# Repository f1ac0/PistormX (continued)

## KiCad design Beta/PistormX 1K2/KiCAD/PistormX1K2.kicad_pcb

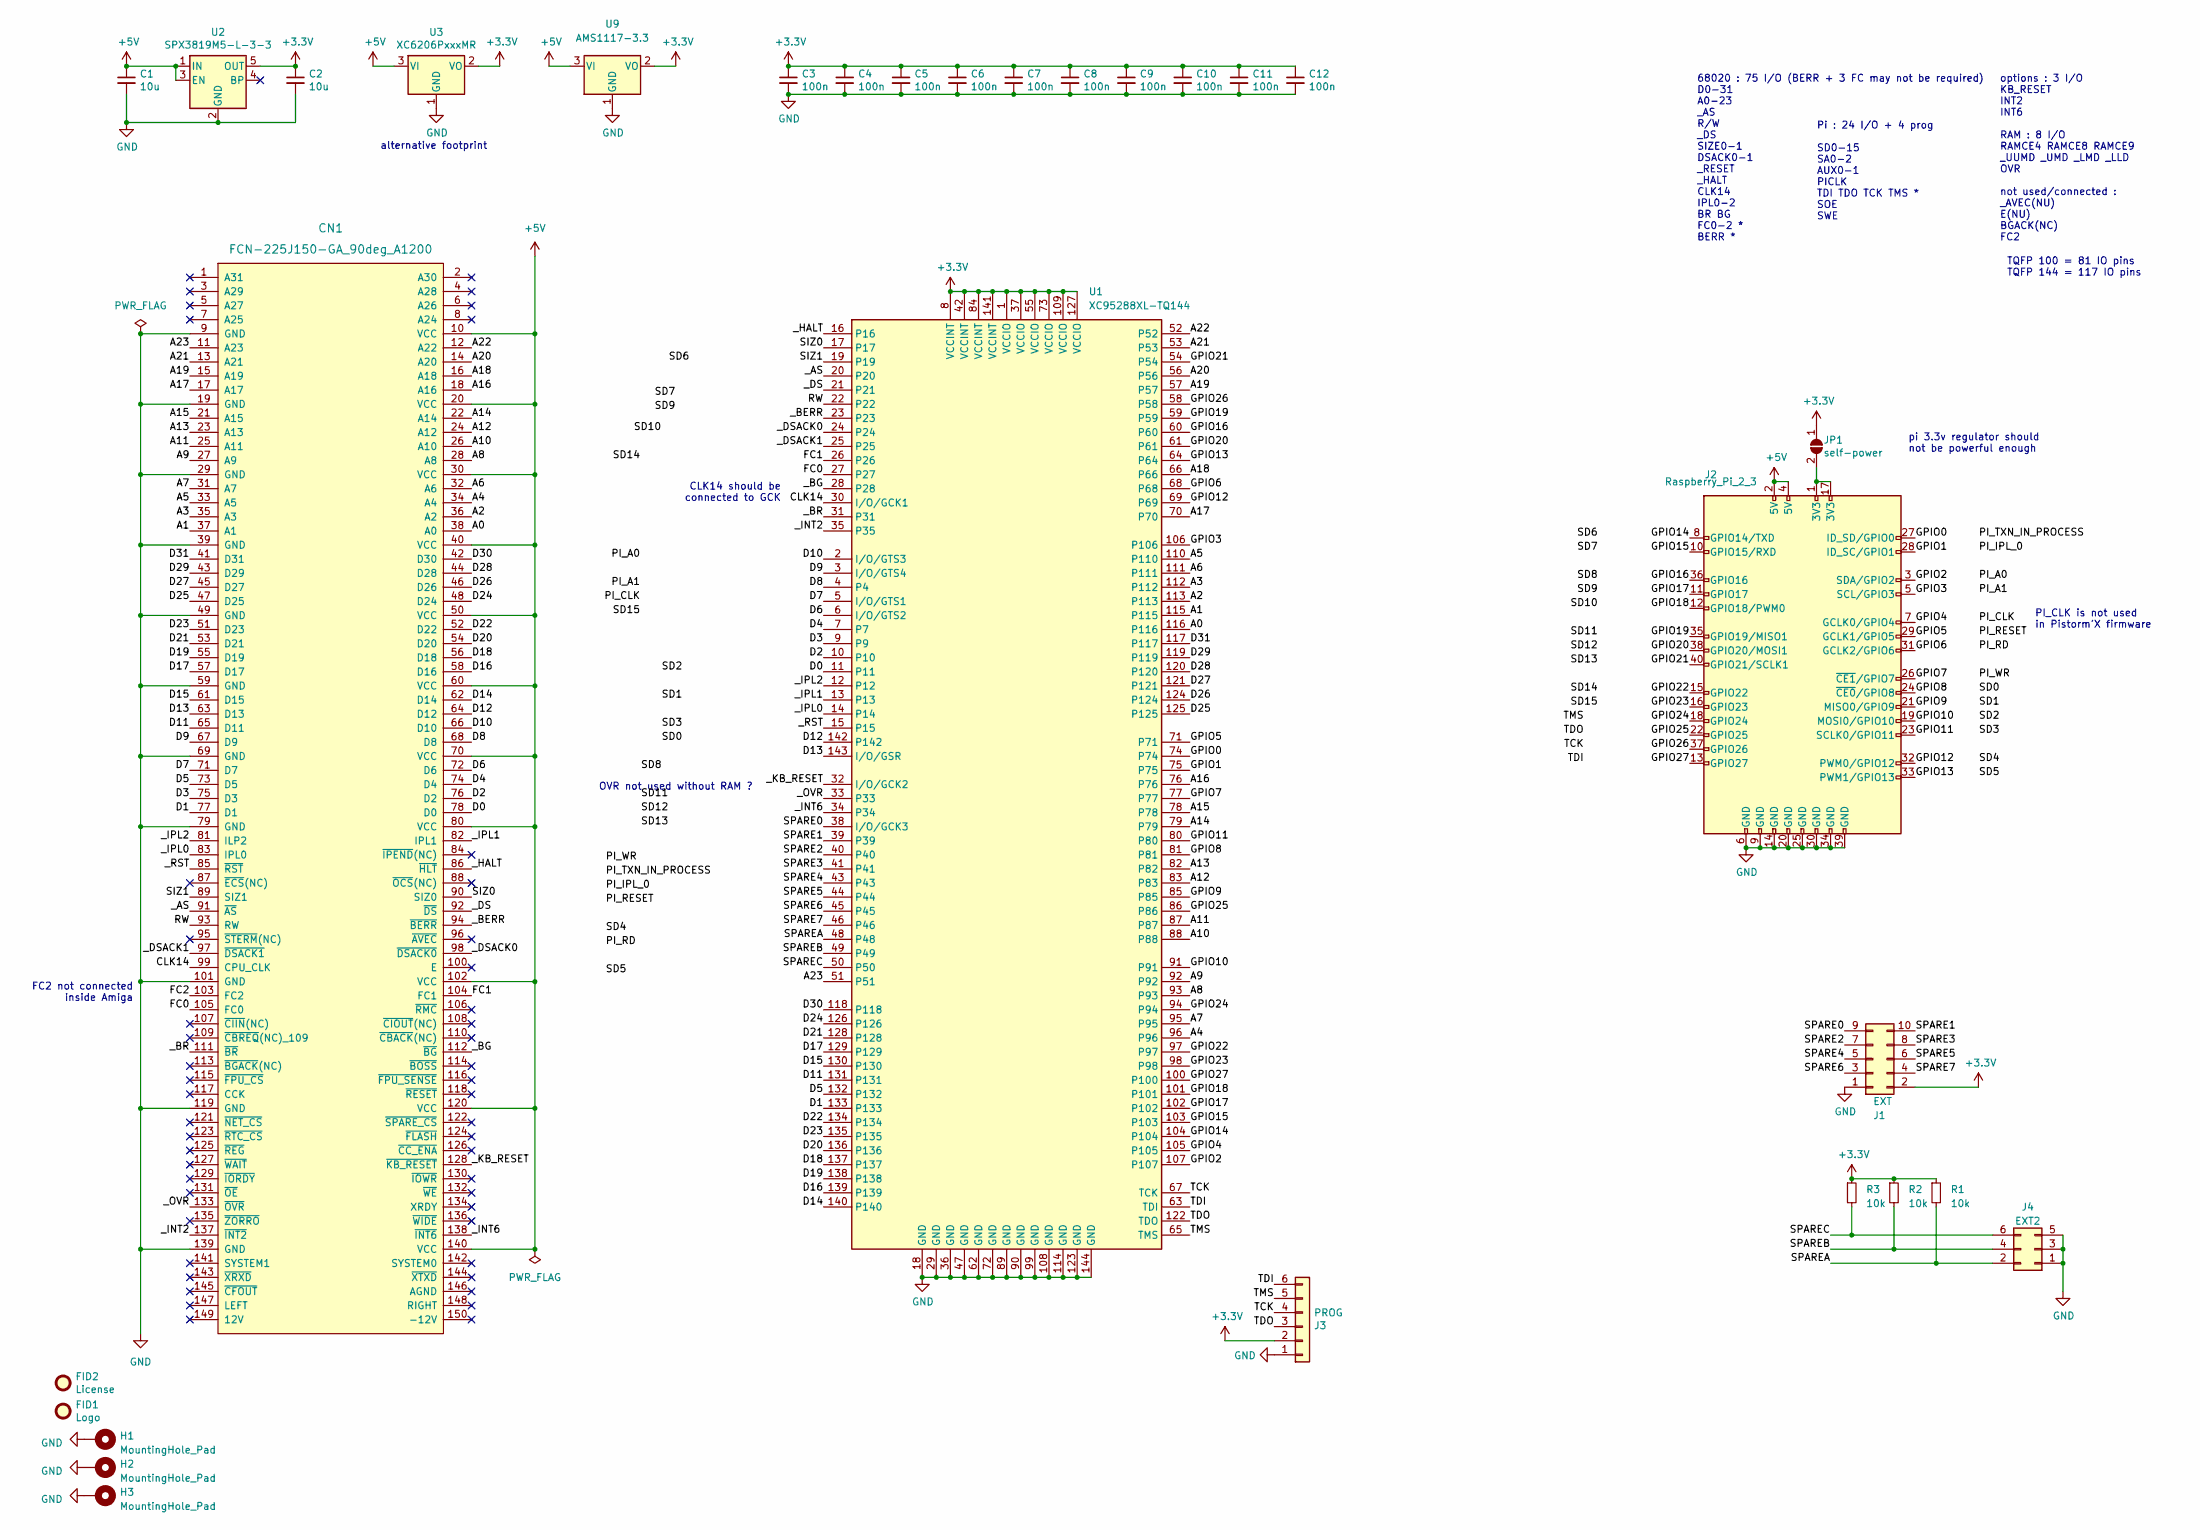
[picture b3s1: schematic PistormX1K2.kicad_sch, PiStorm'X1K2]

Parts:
C1, C2: 10u; C_0805_2012Metric
C3, C4, C5, C6, C7, C8, C9, C10, C11, C12: 100n; C_0603_1608Metric
CN1: FCN-225J150-GA_90deg_A1200
FID1: Logo; PIC_PistormX_43x10mm
FID2: License; CC_BY_NC_SA_square_silkscreen
H1, H2, H3: MountingHole_Pad; MountingHole_2.7mm_M2.5_DIN965_Pad
J1: EXT; PinHeader_2x05_P2.54mm_Vertical
J2: Raspberry_Pi_2_3; PinSocket_2x20_P2.54mm_Vertical_SMD_BottomEntry
J3: PROG; PinHeader_1x06_P2.54mm_Vertical
J4: EXT2; PinHeader_2x03_P2.54mm_Vertical
JP1: self-power; SolderJumper-2_P1.3mm_Open_RoundedPad1.0x1.5mm
R1, R2, R3: 10k; R_0805_2012Metric
U1: XC95288XL-TQ144; TQFP-144_20x20mm_P0.5mm
U2: SPX3819M5-L-3-3; SOT-23-5
U3: XC6206PxxxMR; SOT-23
U9: AMS1117-3.3; SOT-223-3_TabPin2

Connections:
+3.3V: C2.1, C3.1, C4.1, C5.1, C6.1, C7.1, C8.1, C9.1, C10.1, C11.1, C12.1, J1.2, J3.2, JP1.1 (A), R1.1, R2.1, R3.1, U1.1 (VCCIO), U1.8 (VCCINT), U1.37 (VCCIO), U1.42 (VCCINT), U1.55 (VCCIO), U1.73 (VCCIO), U1.84 (VCCINT), U1.109 (VCCIO), U1.127 (VCCIO), U1.141 (VCCINT), U2.5 (OUT), U3.2 (VO), U9.2 (VO)
+5V: C1.1, CN1.10 (VCC), CN1.20 (VCC), CN1.30 (VCC), CN1.40 (VCC), CN1.50 (VCC), CN1.60 (VCC), CN1.70 (VCC), CN1.80 (VCC), CN1.102 (VCC), CN1.120 (VCC), CN1.140 (VCC), J2.2 (5V), J2.4 (5V), U2.1 (IN), U2.3 (EN), U3.3 (VI), U9.3 (VI)
/A0: CN1.38 (A0), U1.116
/A1: CN1.37 (A1), U1.115
/A2: CN1.36 (A2), U1.113
/A3: CN1.35 (A3), U1.112
/A4: CN1.34 (A4), U1.96
/A5: CN1.33 (A5), U1.110
/A6: CN1.32 (A6), U1.111
/A7: CN1.31 (A7), U1.95
/A8: CN1.28 (A8), U1.93
/A9: CN1.27 (A9), U1.92
/A10: CN1.26 (A10), U1.88
/A11: CN1.25 (A11), U1.87
/A12: CN1.24 (A12), U1.83
/A13: CN1.23 (A13), U1.82
/A14: CN1.22 (A14), U1.79
/A15: CN1.21 (A15), U1.78
/A16: CN1.18 (A16), U1.76
/A17: CN1.17 (A17), U1.70
/A18: CN1.16 (A18), U1.66
/A19: CN1.15 (A19), U1.57
/A20: CN1.14 (A20), U1.56
/A21: CN1.13 (A21), U1.53
/A22: CN1.12 (A22), U1.52
/A23: CN1.11 (A23), U1.51
/CLK14: CN1.99 (CPU_CLK), U1.30 (I/O/GCK1)
/D0: CN1.78 (D0), U1.11
/D1: CN1.77 (D1), U1.133
/D2: CN1.76 (D2), U1.10
/D3: CN1.75 (D3), U1.9
/D4: CN1.74 (D4), U1.7
/D5: CN1.73 (D5), U1.132
/D6: CN1.72 (D6), U1.6 (I/O/GTS2)
/D7: CN1.71 (D7), U1.5 (I/O/GTS1)
/D8: CN1.68 (D8), U1.4
/D9: CN1.67 (D9), U1.3 (I/O/GTS4)
/D10: CN1.66 (D10), U1.2 (I/O/GTS3)
/D11: CN1.65 (D11), U1.131
/D12: CN1.64 (D12), U1.142
/D13: CN1.63 (D13), U1.143 (I/O/GSR)
/D14: CN1.62 (D14), U1.140
/D15: CN1.61 (D15), U1.130
/D16: CN1.58 (D16), U1.139
/D17: CN1.57 (D17), U1.129
/D18: CN1.56 (D18), U1.137
/D19: CN1.55 (D19), U1.138
/D20: CN1.54 (D20), U1.136
/D21: CN1.53 (D21), U1.128
/D22: CN1.52 (D22), U1.134
/D23: CN1.51 (D23), U1.135
/D24: CN1.48 (D24), U1.126
/D25: CN1.47 (D25), U1.125
/D26: CN1.46 (D26), U1.124
/D27: CN1.45 (D27), U1.121
/D28: CN1.44 (D28), U1.120
/D29: CN1.43 (D29), U1.119
/D30: CN1.42 (D30), U1.118
/D31: CN1.41 (D31), U1.117
/FC0: CN1.105 (FC0), U1.27
/FC1: CN1.104 (FC1), U1.26
/FC2: CN1.103 (FC2)
/GPIO0: J2.27 (ID_SD/GPIO0), U1.74
/GPIO1: J2.28 (ID_SC/GPIO1), U1.75
/GPIO2: J2.3 (SDA/GPIO2), U1.107
/GPIO3: J2.5 (SCL/GPIO3), U1.106
/GPIO4: J2.7 (GCLK0/GPIO4), U1.105
/GPIO5: J2.29 (GCLK1/GPIO5), U1.71
/GPIO6: J2.31 (GCLK2/GPIO6), U1.68
/GPIO7: J2.26 (~CE1/GPIO7), U1.77
/GPIO8: J2.24 (~CE0/GPIO8), U1.81
/GPIO9: J2.21 (MISO0/GPIO9), U1.85
/GPIO10: J2.19 (MOSI0/GPIO10), U1.91
/GPIO11: J2.23 (SCLK0/GPIO11), U1.80
/GPIO12: J2.32 (PWM0/GPIO12), U1.69
/GPIO13: J2.33 (PWM1/GPIO13), U1.64
/GPIO14: J2.8 (GPIO14/TXD), U1.104
/GPIO15: J2.10 (GPIO15/RXD), U1.103
/GPIO16: J2.36 (GPIO16), U1.60
/GPIO17: J2.11 (GPIO17), U1.102
/GPIO18: J2.12 (GPIO18/PWM0), U1.101
/GPIO19: J2.35 (GPIO19/MISO1), U1.59
/GPIO20: J2.38 (GPIO20/MOSI1), U1.61
/GPIO21: J2.40 (GPIO21/SCLK1), U1.54
/GPIO22: J2.15 (GPIO22), U1.97
/GPIO23: J2.16 (GPIO23), U1.98
/GPIO24: J2.18 (GPIO24), U1.94
/GPIO25: J2.22 (GPIO25), U1.86
/GPIO26: J2.37 (GPIO26), U1.58
/GPIO27: J2.13 (GPIO27), U1.100
/RW: CN1.93 (RW), U1.22
/SIZ0: CN1.90 (SIZ0), U1.17
/SIZ1: CN1.89 (SIZ1), U1.19
/SPARE0: J1.9, U1.38 (I/O/GCK3)
/SPARE1: J1.10, U1.39
/SPARE2: J1.7, U1.40
/SPARE3: J1.8, U1.41
/SPARE4: J1.5, U1.43
/SPARE5: J1.6, U1.44
/SPARE6: J1.3, U1.45
/SPARE7: J1.4, U1.46
/SPAREA: J4.2, R1.2, U1.48
/SPAREB: J4.4, R2.2, U1.49
/SPAREC: J4.6, R3.2, U1.50
/TCK: J3.4, U1.67 (TCK)
/TDI: J3.6, U1.63 (TDI)
/TDO: J3.3, U1.122 (TDO)
/TMS: J3.5, U1.65 (TMS)
/_AS: CN1.91 (~AS), U1.20
/_BERR: CN1.94 (~BERR), U1.23
/_BG: CN1.112 (~BG), U1.28
/_BR: CN1.111 (~BR), U1.31
/_DS: CN1.92 (~DS), U1.21
/_DSACK0: CN1.98 (~DSACK0), U1.24
/_DSACK1: CN1.97 (~DSACK1), U1.25
/_HALT: CN1.86 (~HLT), U1.16
/_INT2: CN1.137 (~INT2), U1.35
/_INT6: CN1.138 (~INT6), U1.34
/_IPL0: CN1.83 (IPL0), U1.14
/_IPL1: CN1.82 (IPL1), U1.13
/_IPL2: CN1.81 (ILP2), U1.12
/_KB_RESET: CN1.128 (~KB_RESET), U1.32 (I/O/GCK2)
/_OVR: CN1.133 (~OVR), U1.33
/_RST: CN1.85 (~RST), U1.15
GND: C1.2, C2.2, C3.2, C4.2, C5.2, C6.2, C7.2, C8.2, C9.2, C10.2, C11.2, C12.2, CN1.9 (GND), CN1.19 (GND), CN1.29 (GND), CN1.39 (GND), CN1.49 (GND), CN1.59 (GND), CN1.69 (GND), CN1.79 (GND), CN1.101 (GND), CN1.119 (GND), CN1.139 (GND), H1.1, H2.1, H3.1, J1.1, J2.6 (GND), J2.9 (GND), J2.14 (GND), J2.20 (GND), J2.25 (GND), J2.30 (GND), J2.34 (GND), J2.39 (GND), J3.1, J4.1, J4.3, J4.5, U1.18 (GND), U1.29 (GND), U1.36 (GND), U1.47 (GND), U1.62 (GND), U1.72 (GND), U1.89 (GND), U1.90 (GND), U1.99 (GND), U1.108 (GND), U1.114 (GND), U1.123 (GND), U1.144 (GND), U2.2 (GND), U3.1 (GND), U9.1 (GND)
unnamed: J2.1 (3V3), J2.17 (3V3), JP1.2 (B)

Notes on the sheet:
CLK14 should be connected to GCK
Pi : 24 I/O + 4 prog SD0-15 SA0-2 AUX0-1 PICLK TDI TDO TCK TMS * SOE SWE
OVR not used without RAM ?
FC2 not connected inside Amiga
alternative footprint
pi 3.3v regulator should not be powerful enough
TQFP 100 = 81 IO pins TQFP 144 = 117 IO pins
68020 : 75 I/O (BERR + 3 FC may not be required) D0-31 A0-23 _AS R/W _DS SIZE0-1 DSACK0-1 _RESET _HALT CLK14 IPL0-2 BR BG FC0-2 * BERR *
options : 3 I/O KB_RESET INT2 INT6 RAM : 8 I/O RAMCE4 RAMCE8 RAMCE9 _UUMD _UMD _LMD _LLD OVR not used/connected : _AVEC(NU) E(NU) BGACK(NC) FC2
PI_CLK is not used in Pistorm'X firmware

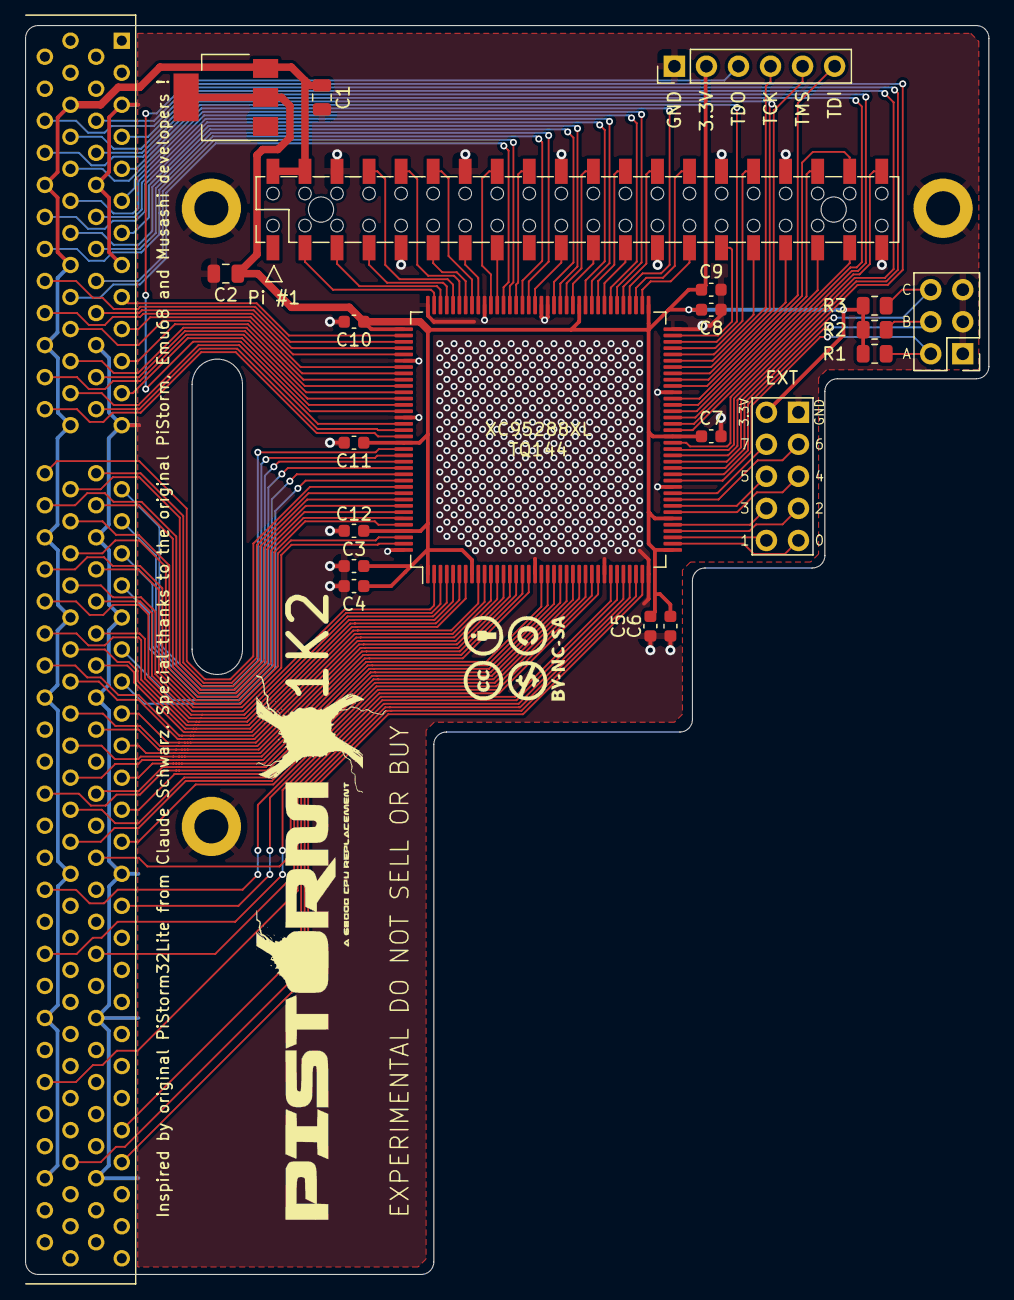
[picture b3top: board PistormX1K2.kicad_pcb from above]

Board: 2 copper layers, 76.4 x 99.0 mm, 27 parts (1 on the bottom side), 125 nets.

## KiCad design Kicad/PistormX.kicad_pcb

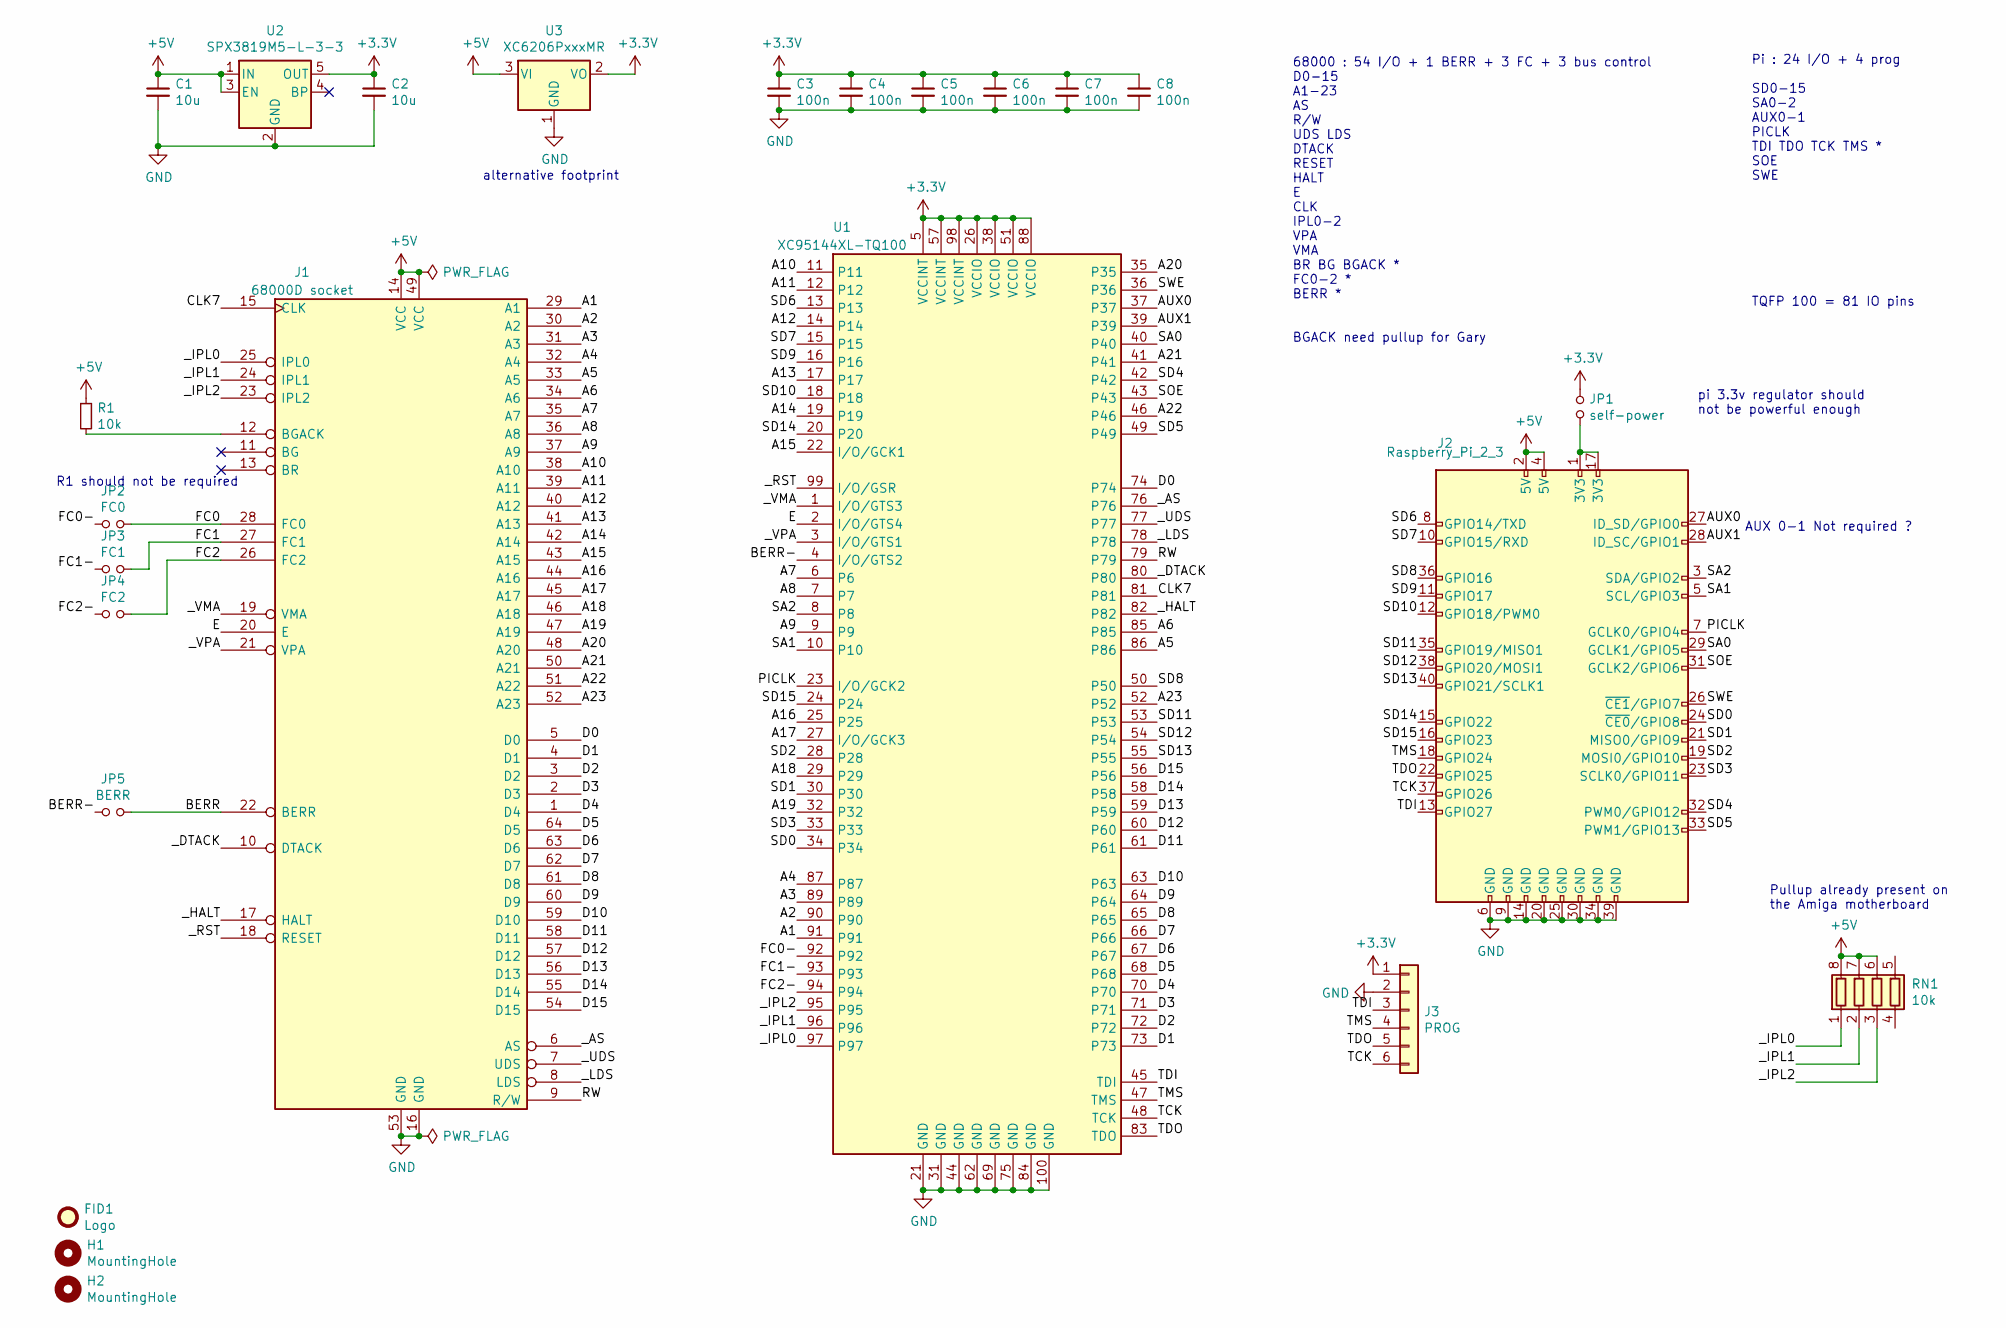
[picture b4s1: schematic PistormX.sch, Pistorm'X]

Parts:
C1, C2: 10u; C_0805_2012Metric
C3, C4, C5, C6, C7, C8: 100n; C_0805_2012Metric
FID1: Logo; PistormX
H1, H2: MountingHole; MountingHole_2.5mm
J1: 68000D socket; DIP-64_W22.86mm_BigPads1.4
J2: Raspberry_Pi_2_3; PinSocket_2x20_P2.54mm_Vertical
J3: PROG; PinHeader_1x06_P2.54mm_Vertical
JP1: self-power; SolderJumper-2_P1.3mm_Open_RoundedPad1.0x1.5mm
JP2: FC0; SolderJumper-2_P1.3mm_Open_RoundedPad1.0x1.5mm
JP3: FC1; SolderJumper-2_P1.3mm_Open_RoundedPad1.0x1.5mm
JP4: FC2; SolderJumper-2_P1.3mm_Open_RoundedPad1.0x1.5mm
JP5: BERR; SolderJumper-2_P1.3mm_Open_RoundedPad1.0x1.5mm
R1: 10k; R_0805_2012Metric
RN1: 10k; R_Array_Convex_4x0603
U1: XC95144XL-TQ100; TQFP-100_14x14mm_P0.5mm
U2: SPX3819M5-L-3-3; SOT-23-5
U3: XC6206PxxxMR; SOT-23

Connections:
+3V3: C2.1, C3.1, C4.1, C5.1, C6.1, C7.1, C8.1, J3.1, JP1.1, U1.5 (VCCINT), U1.26 (VCCIO), U1.38 (VCCIO), U1.51 (VCCIO), U1.57 (VCCINT), U1.88 (VCCIO), U1.98 (VCCINT), U2.5 (OUT), U3.2 (VO)
+5V: C1.1, J1.14 (VCC), J1.49 (VCC), J2.2 (5V), J2.4 (5V), R1.1, RN1.6 (R3.2), RN1.7 (R2.2), RN1.8 (R1.2), U2.1 (IN), U2.3 (EN), U3.3 (VI)
/A1: J1.29 (A1), U1.91
/A2: J1.30 (A2), U1.90
/A3: J1.31 (A3), U1.89
/A4: J1.32 (A4), U1.87
/A5: J1.33 (A5), U1.86
/A6: J1.34 (A6), U1.85
/A7: J1.35 (A7), U1.6
/A8: J1.36 (A8), U1.7
/A9: J1.37 (A9), U1.9
/A10: J1.38 (A10), U1.11
/A11: J1.39 (A11), U1.12
/A12: J1.40 (A12), U1.14
/A13: J1.41 (A13), U1.17
/A14: J1.42 (A14), U1.19
/A15: J1.43 (A15), U1.22 (I/O/GCK1)
/A16: J1.44 (A16), U1.25
/A17: J1.45 (A17), U1.27 (I/O/GCK3)
/A18: J1.46 (A18), U1.29
/A19: J1.47 (A19), U1.32
/A20: J1.48 (A20), U1.35
/A21: J1.50 (A21), U1.41
/A22: J1.51 (A22), U1.46
/A23: J1.52 (A23), U1.52
/BERR: J1.22 (BERR), JP5.2 (B)
/BERR-: JP5.1 (A), U1.4 (I/O/GTS2)
/CLK7: J1.15 (CLK), U1.81
/D0: J1.5 (D0), U1.74
/D1: J1.4 (D1), U1.73
/D2: J1.3 (D2), U1.72
/D3: J1.2 (D3), U1.71
/D4: J1.1 (D4), U1.70
/D5: J1.64 (D5), U1.68
/D6: J1.63 (D6), U1.67
/D7: J1.62 (D7), U1.66
/D8: J1.61 (D8), U1.65
/D9: J1.60 (D9), U1.64
/D10: J1.59 (D10), U1.63
/D11: J1.58 (D11), U1.61
/D12: J1.57 (D12), U1.60
/D13: J1.56 (D13), U1.59
/D14: J1.55 (D14), U1.58
/D15: J1.54 (D15), U1.56
/E: J1.20 (E), U1.2 (I/O/GTS4)
/FC0: J1.28 (FC0), JP2.2 (B)
/FC0-: JP2.1 (A), U1.92
/FC1: J1.27 (FC1), JP3.2 (B)
/FC1-: JP3.1 (A), U1.93
/FC2: J1.26 (FC2), JP4.2 (B)
/FC2-: JP4.1 (A), U1.94
/PI_A0: J2.3 (SDA/GPIO2), U1.8
/PI_A1: J2.5 (SCL/GPIO3), U1.10
/PI_CLK: J2.7 (GCLK0/GPIO4), U1.23 (I/O/GCK2)
/PI_IPL_0: J2.28 (ID_SC/GPIO1), U1.39
/PI_RD: J2.31 (GCLK2/GPIO6), U1.43
/PI_RESET: J2.29 (GCLK1/GPIO5), U1.40
/PI_TXN_IN_PROCESS: J2.27 (ID_SD/GPIO0), U1.37
/PI_WR: J2.26 (~CE1/GPIO7), U1.36
/RW: J1.9 (R/W), U1.79
/SD0: J2.24 (~CE0/GPIO8), U1.34
/SD1: J2.21 (MISO0/GPIO9), U1.30
/SD2: J2.19 (MOSI0/GPIO10), U1.28
/SD3: J2.23 (SCLK0/GPIO11), U1.33
/SD4: J2.32 (PWM0/GPIO12), U1.42
/SD5: J2.33 (PWM1/GPIO13), U1.49
/SD6: J2.8 (GPIO14/TXD), U1.13
/SD7: J2.10 (GPIO15/RXD), U1.15
/SD8: J2.36 (GPIO16), U1.50
/SD9: J2.11 (GPIO17), U1.16
/SD10: J2.12 (GPIO18/PWM0), U1.18
/SD11: J2.35 (GPIO19/MISO1), U1.53
/SD12: J2.38 (GPIO20/MOSI1), U1.54
/SD13: J2.40 (GPIO21/SCLK1), U1.55
/SD14: J2.15 (GPIO22), U1.20
/SD15: J2.16 (GPIO23), U1.24
/TCK: J2.37 (GPIO26), J3.6, U1.48 (TCK)
/TDI: J2.13 (GPIO27), J3.3, U1.45 (TDI)
/TDO: J2.22 (GPIO25), J3.5, U1.83 (TDO)
/TMS: J2.18 (GPIO24), J3.4, U1.47 (TMS)
/_AS: J1.6 (AS), U1.76
/_DTACK: J1.10 (DTACK), U1.80
/_HALT: J1.17 (HALT), U1.82
/_IPL0: J1.25 (IPL0), RN1.1 (R1.1), U1.97
/_IPL1: J1.24 (IPL1), RN1.2 (R2.1), U1.96
/_IPL2: J1.23 (IPL2), RN1.3 (R3.1), U1.95
/_LDS: J1.8 (LDS), U1.78
/_RST: J1.18 (RESET), U1.99 (I/O/GSR)
/_UDS: J1.7 (UDS), U1.77
/_VMA: J1.19 (VMA), U1.1 (I/O/GTS3)
/_VPA: J1.21 (VPA), U1.3 (I/O/GTS1)
GND: C1.2, C2.2, C3.2, C4.2, C5.2, C6.2, C7.2, C8.2, J1.16 (GND), J1.53 (GND), J2.6 (GND), J2.9 (GND), J2.14 (GND), J2.20 (GND), J2.25 (GND), J2.30 (GND), J2.34 (GND), J2.39 (GND), J3.2, U1.21 (GND), U1.31 (GND), U1.44 (GND), U1.62 (GND), U1.69 (GND), U1.75 (GND), U1.84 (GND), U1.100 (GND), U2.2 (GND), U3.1 (GND)
unnamed: J1.12 (BGACK), R1.2
unnamed: J2.1 (3V3), J2.17 (3V3), JP1.2

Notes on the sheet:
Pi : 24 I/O + 4 prog SD0-15 SA0-2 AUX0-1 PICLK TDI TDO TCK TMS * SOE SWE
68000 : 54 I/O + 1 BERR + 3 FC + 3 bus control D0-15 A1-23 AS R/W UDS LDS DTACK RESET HALT E CLK IPL0-2 VPA VMA BR BG BGACK * FC0-2 * BERR * BGACK need pullup for Gary
TQFP 100 = 81 IO pins
alternative footprint
R1 should not be required
AUX 0-1 Not required ?
Pullup already present on the Amiga motherboard
pi 3.3v regulator should not be powerful enough

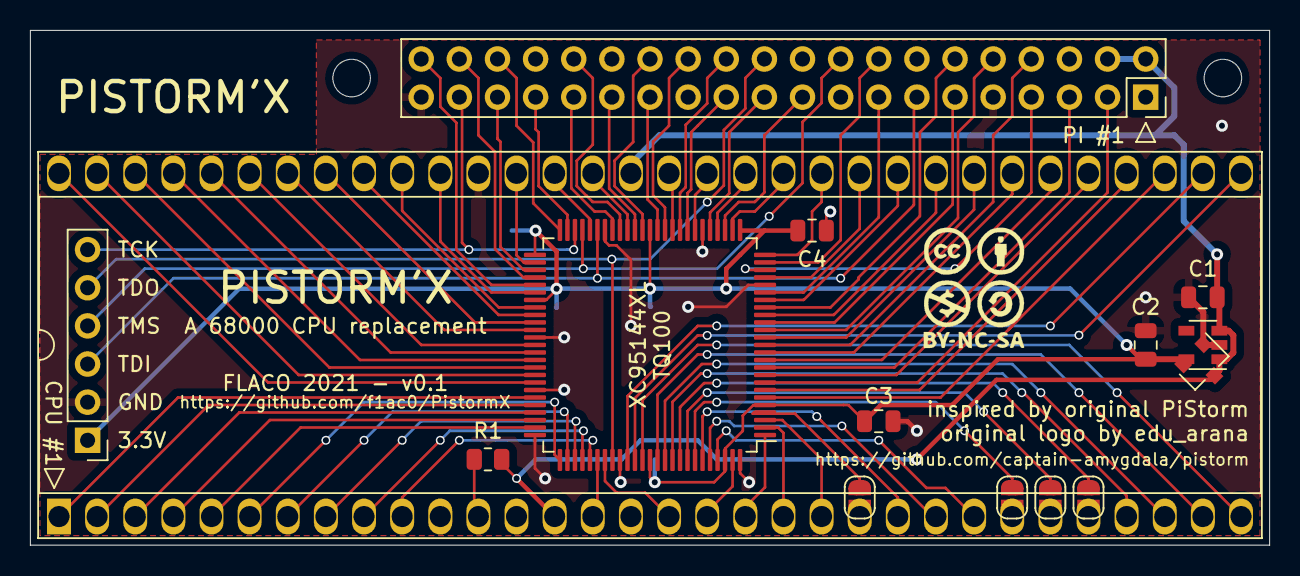
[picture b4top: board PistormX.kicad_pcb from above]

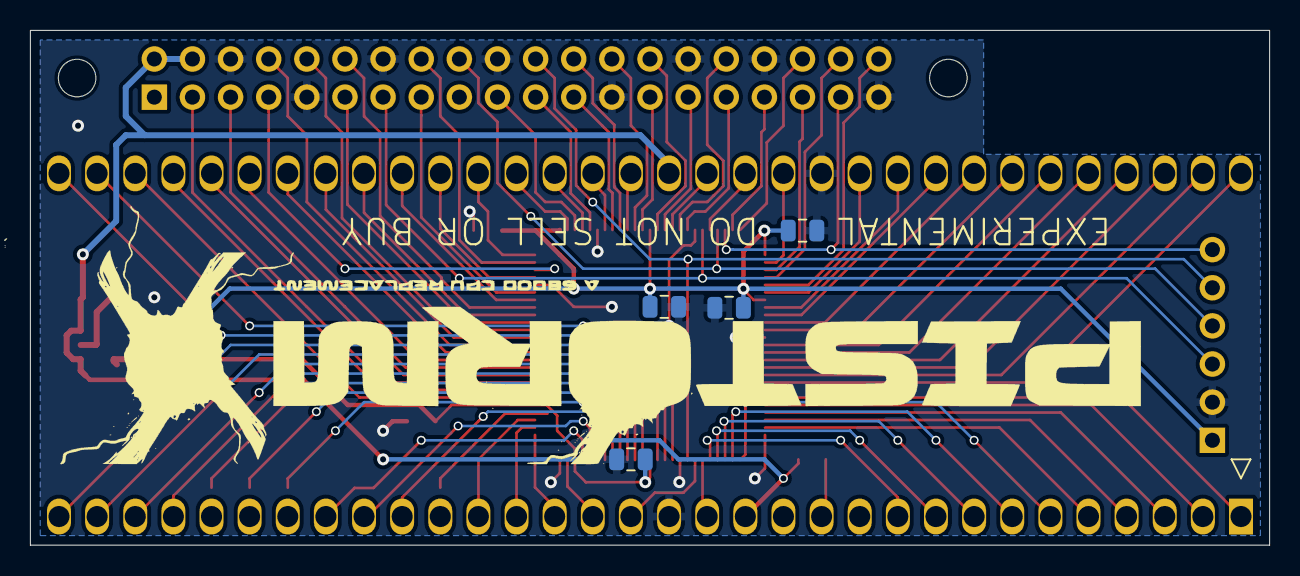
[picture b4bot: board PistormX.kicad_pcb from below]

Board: 2 copper layers, 82.6 x 34.3 mm, 23 parts (5 on the bottom side), 94 nets.

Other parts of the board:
FID2: License; CC_BY_NC_SA_square_silkscreen

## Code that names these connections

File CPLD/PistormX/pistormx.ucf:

NET PI_TXN_IN_PROGRESS LOC=P37;
NET PI_IPL_ZERO LOC=P39;
NET PI_A<1> LOC=P10;
NET PI_A<0> LOC=P8;
//NET PI_CLK LOC=P23;
NET PI_RESET LOC=P40;
NET PI_RD LOC=P43;
NET PI_WR LOC=P36;
NET PI_D<15> LOC=P24;
NET PI_D<14> LOC=P20;
NET PI_D<13> LOC=P55;
NET PI_D<12> LOC=P54;
NET PI_D<11> LOC=P53;
NET PI_D<10> LOC=P18;
NET PI_D<9> LOC=P16;
NET PI_D<8> LOC=P50;
NET PI_D<7> LOC=P15;
NET PI_D<6> LOC=P13;
NET PI_D<5> LOC=P49;
NET PI_D<4> LOC=P42;
NET PI_D<3> LOC=P33;
NET PI_D<2> LOC=P28;
NET PI_D<1> LOC=P30;
NET PI_D<0> LOC=P34;

NET M68K_A<23> LOC=P52;
NET M68K_A<22> LOC=P46;
NET M68K_A<21> LOC=P41;
NET M68K_A<20> LOC=P35;
NET M68K_A<19> LOC=P32;
NET M68K_A<18> LOC=P29;
NET M68K_A<17> LOC=P27;
NET M68K_A<16> LOC=P25;
NET M68K_A<15> LOC=P22;
NET M68K_A<14> LOC=P19;
NET M68K_A<13> LOC=P17;
NET M68K_A<12> LOC=P14;
NET M68K_A<11> LOC=P12;
NET M68K_A<10> LOC=P11;
NET M68K_A<9> LOC=P9;
NET M68K_A<8> LOC=P7;
NET M68K_A<7> LOC=P6;
NET M68K_A<6> LOC=P85;
NET M68K_A<5> LOC=P86;
NET M68K_A<4> LOC=P87;
NET M68K_A<3> LOC=P89;
NET M68K_A<2> LOC=P90;
NET M68K_A<1> LOC=P91;
NET M68K_D<15> LOC=P56;
NET M68K_D<14> LOC=P58;
NET M68K_D<13> LOC=P59;
NET M68K_D<12> LOC=P60;
NET M68K_D<11> LOC=P61;
NET M68K_D<10> LOC=P63;
NET M68K_D<9> LOC=P64;
NET M68K_D<8> LOC=P65;
NET M68K_D<7> LOC=P66;
NET M68K_D<6> LOC=P67;
NET M68K_D<5> LOC=P68;
NET M68K_D<4> LOC=P70;
NET M68K_D<3> LOC=P71;
NET M68K_D<2> LOC=P72;
NET M68K_D<1> LOC=P73;
NET M68K_D<0> LOC=P74;
NET M68K_CLK LOC=P81;
//NET M68K_FC<2> LOC=P94;
//NET M68K_FC<1> LOC=P93;
//NET M68K_FC<0> LOC=P92;

NET M68K_AS_n LOC=P76;
NET M68K_UDS_n LOC=P77;
NET M68K_LDS_n LOC=P78;
NET M68K_RW LOC=P79;

NET M68K_DTACK_n LOC=P80;
//NET M68K_BERR_n LOC=P4;

NET M68K_VPA_n LOC=P3;
NET M68K_E LOC=P2;
NET M68K_VMA_n LOC=P1;

NET M68K_IPL_n<2> LOC=P95;
NET M68K_IPL_n<1> LOC=P96;
NET M68K_IPL_n<0> LOC=P97;

NET M68K_RESET_n LOC=P99;
NET M68K_HALT_n LOC=P82;

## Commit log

2021-07-27 Respository init with KiCAD files, CPLD files, Readme and License
2022-02-08 Kicad : first board revision ; CPLD : working with buptest and emulator, no 200MHz PICLK is used, fixed cold and warm reset
2022-02-11 CPLD : new version with write buffer ; cleanup in original version
2022-02-13 Kicad: converted to v6, relabeled the Pi signals in schematic, added EXPERIMENTAL and CC-BY-NC-SA on silkscreen ; CPLD: add JED files ; Photo
2022-02-14 Kicad: Gerbers and InteractiveHtmlBom
2022-02-15 README
2022-02-19 Firmare : fix basic firmware not working because TX_IN_PROCESS was released too early ; fix A bus was set when waiting in S1 ; new experimental firmwares
2022-02-24 Pistorm firmare : added Pistorm'X firmwares for the original Pistorm CPU board
2022-03-01 Pistorm firmare : firmwares for original Pistorm CPU board are now booting in both Musashi and EMU68 but are unstable :(
2022-03-04 Firmare : new 4 states cycle firmware ; remove the 8 states cycle write buffer firmware ; change VPA cycle in 6 states cycle firmwares ; code and namining cleanup
2022-11-14 Pistorm'X 68k debut ; Pistorm'X 4 states cycle without write buffer firmware
2022-11-20 Pistorm'X-68k : improved reset handling, detection of the Pi emulator, and use E clock for long reset count ; update Readme
2022-11-22 Pistorm'X-68k : changed E clock detection that was not working as expected, code cleanup ; tested with and without 68000
2023-05-23 New Beta untested boards and firmwares : PiStorm'X 500, PiStorm'X 600 and PiStorm'X 1K2. See README.
2023-05-25 Added an alternative board layout for the Pistorm'X 1K2. Some cleanup on the first PiStorm'X 1K2 board. Updated README.
2023-06-03 Pistorm'X DMA debut ; PiStorm'X firmware for the original board with support for Bus Arbitration signals, to hopefully work with DMA peripherals in A2000
2023-10-12 Pistorm'X DMA : renamed the firmware files to indicate the original one they are based on '4 states cycle write buffer' and add the '6 states cycle write buffer' counterpart
2023-10-13 Pistorm'X DMA : added the '8 states cycle' logic for testing purposes
2024-02-22 PiStorm'X 500 and PiStorm'X 600 corrections. PiStorm'X 600 is actually working and under test. PiStorm'X 500 will be tested after I find an Agnus 8375 or A500 motherboard replacement.
2024-05-08 PiStorm'X 500 DIP : finally working firmware, changed 7MHz clock input pin, adjustments to VMA timing, cleanup. PiStorm'X 600 cleanup. Original PiStorm'X for A500 moved to 'Alpha' folder.
2024-11-27 PiStorm'X 500 DIP : some adjustments that I hoped would help reduce heat from the CPLD. Not much difference according to my measurements but at least reduces FB inps and Pterms (-27 and -23 respectiv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
2024-12-07 PiStorm'X 500 DIP & PiStorm'X 600: more power adjustments that may reduce heat from the CPLD.
